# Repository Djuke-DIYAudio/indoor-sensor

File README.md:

# Indoor sensor
This project contains the open source design files of an affordable indoor air sensor that can accurately measure CO2 level, Temperature, Humidity and Pressure. It contains a ESP8266 wi-fi module making it easy to integrate with your home automation system. 

Possible use cases:
* Monitoring sensor values over time
* Switching of air ventilation based on CO2 or humidity level
* Regulating room temperature (airco or heater)

# Design

## Considerations
At the moment the design considerations are:

* MH-Z19 sensor for measuring CO2 ppm
* BME280 sensor for measuring temperature, humidity and pressure sensor
* ESP8266 module to easily integrate with WIFI in the smart home
* red/green dual LED for level indication
  - Green, PPM < 800
  - Yellow/Orange, 800 < PPM < 1400
  - Red, PPM > 1400
* Connectors for optional 0.91 inch or 0.96 inch SSD1306 display
* Sales price around 25 euros

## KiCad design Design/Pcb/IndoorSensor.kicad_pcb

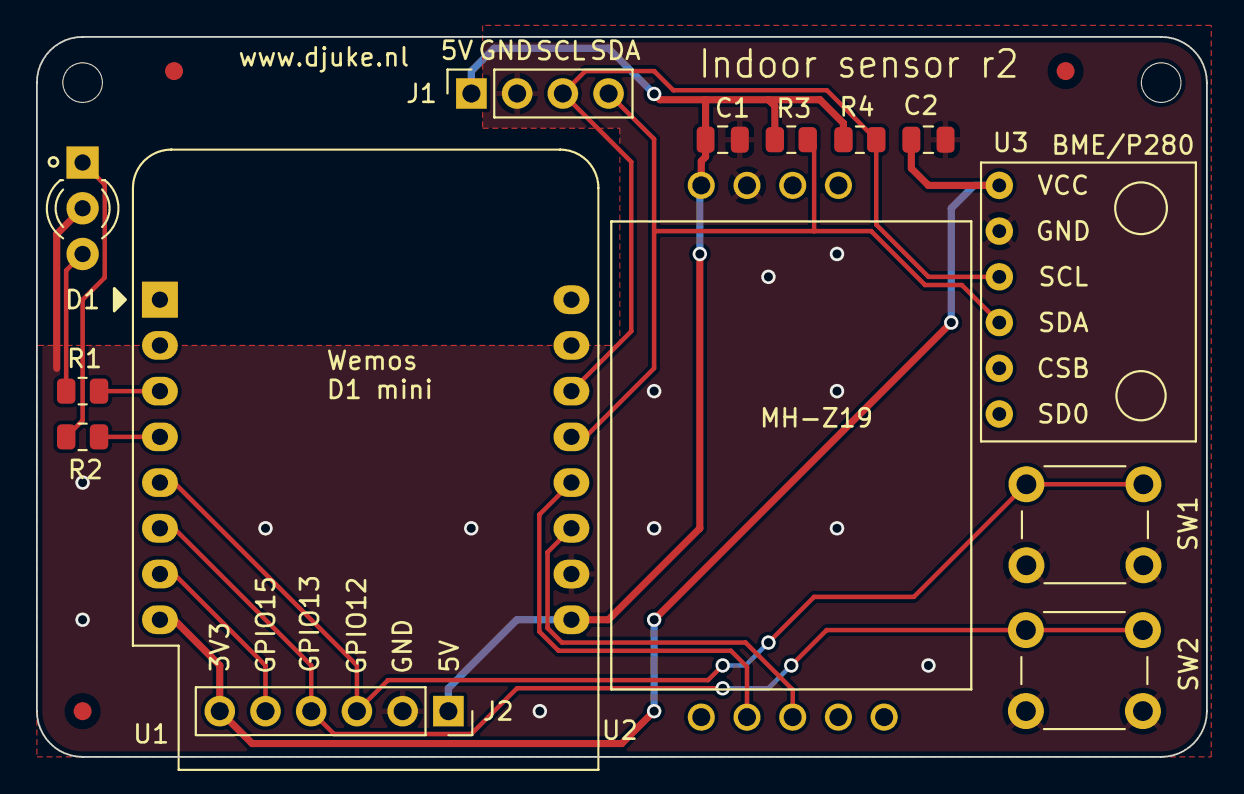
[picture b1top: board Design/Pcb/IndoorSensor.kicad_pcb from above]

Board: 2 copper layers, 65.0 x 40.0 mm, 19 parts (0 on the bottom side), 14 nets.

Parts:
C1, C2: 100n; C_0805_2012Metric
D1: LED_Dual_AKA; LED_D3.0mm-3
FID1, FID2, FID3: Fiducial; Fiducial_1mm_Mask2mm
H1, H2: MountingHole; MountingHole_2.2mm_M2
J1: Conn_01x04_Pin; PinSocket_1x04_P2.54mm_Vertical
J2: Conn_01x06_Pin; PinSocket_1x06_P2.54mm_Vertical
R1, R2: 220; R_0805_2012Metric
R3, R4: 4k7; R_0805_2012Metric
SW1, SW2: SW_Push; SW_PUSH_6mm_H5mm
U1: WeMos_D1_mini; WEMOS_D1_mini_light
U2: MH-Z19B; MH-Z19B-FOOT
U3: module_bme280

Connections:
+3V3: C2.1, J2.6, U1.8 (3V3), U3.1 (VCC)
+5V: C1.1, J1.1, J2.1, R3.2, R4.2, U1.9 (5V), U2.VIN
GND: C1.2, C2.2, D1.2 (K), J1.2, J2.2, SW1.2, SW2.2, U1.10 (GND), U2.GND, U3.2 (GND)
GPIO12: J2.3, SW1.1, U1.5 (MISO/D6)
GPIO13: J2.4, SW2.1, U1.6 (MOSI/D7)
GPIO15: J2.5, U1.7 (CS/D8)
LED_ERR: R2.1, U1.4 (SCK/D5)
LED_OK: R1.1, U1.3 (D0)
unnamed: D1.1 (A1), R2.2
unnamed: D1.3 (A2), R1.2
RX: U1.11 (D4), U2.TX
SCL: J1.3, R4.1, U1.14 (SCL/D1), U3.3 (SCL)
SDA: J1.4, R3.1, U1.13 (SDA/D2), U3.4 (SDA)
TX: U1.12 (D3), U2.RX

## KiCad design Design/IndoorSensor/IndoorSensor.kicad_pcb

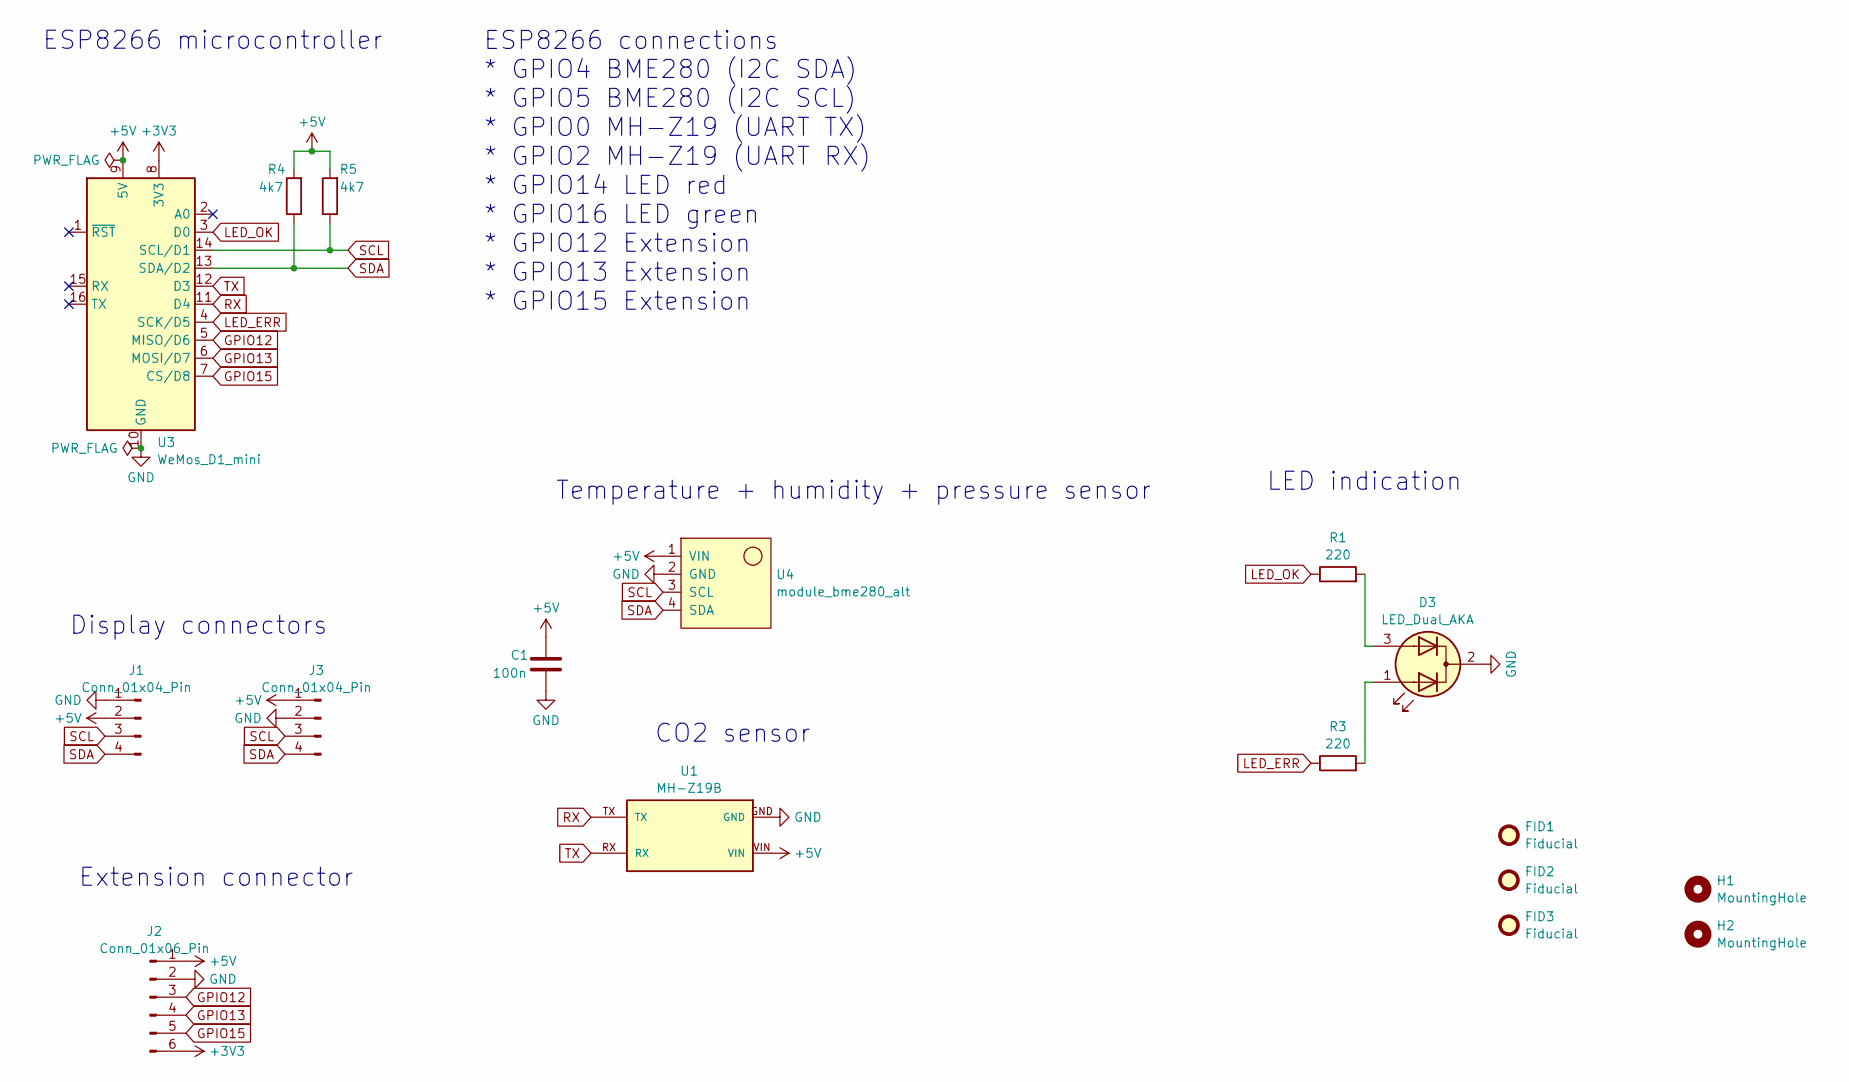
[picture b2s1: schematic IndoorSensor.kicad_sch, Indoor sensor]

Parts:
C1: 100n; C_0805_2012Metric
D3: LED_Dual_AKA; LED_D3.0mm-3
FID1, FID2, FID3: Fiducial; Fiducial_1mm_Mask2mm
H1, H2: MountingHole; MountingHole_2.2mm_M2
J1, J3: Conn_01x04_Pin; PinSocket_1x04_P2.54mm_Vertical
J2: Conn_01x06_Pin; PinHeader_1x06_P2.54mm_Vertical
R1, R3: 220; R_0805_2012Metric
R4, R5: 4k7; R_0805_2012Metric
U1: MH-Z19B; MH-Z19B-FOOT
U3: WeMos_D1_mini; WEMOS_D1_mini_light
U4: module_bme280_alt

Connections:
+3V3: J2.6, U3.8 (3V3)
+5V: C1.1, J1.2, J2.1, J3.1, R4.2, R5.2, U1.VIN, U3.9 (5V), U4.1 (VIN)
GND: C1.2, D3.2 (K), J1.1, J2.2, J3.2, U1.GND, U3.10 (GND), U4.2 (GND)
GPIO12: J2.3, U3.5 (MISO/D6)
GPIO13: J2.4, U3.6 (MOSI/D7)
GPIO15: J2.5, U3.7 (CS/D8)
LED_ERR: R3.1, U3.4 (SCK/D5)
LED_OK: R1.1, U3.3 (D0)
unnamed: D3.1 (A1), R3.2
unnamed: D3.3 (A2), R1.2
RX: U1.TX, U3.11 (D4)
SCL: J1.3, J3.3, R5.1, U3.14 (SCL/D1), U4.3 (SCL)
SDA: J1.4, J3.4, R4.1, U3.13 (SDA/D2), U4.4 (SDA)
TX: U1.RX, U3.12 (D3)

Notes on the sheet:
Temperature + humidity + pressure sensor
ESP8266 connections * GPIO4 BME280 (I2C SDA) * GPIO5 BME280 (I2C SCL) * GPIO0 MH-Z19 (UART TX) * GPIO2 MH-Z19 (UART RX) * GPIO14 LED red * GPIO16 LED green * GPIO12 Extension * GPIO13 Extension * GPIO15 Extension
ESP8266 microcontroller
LED indication
Extension connector
CO2 sensor
Display connectors

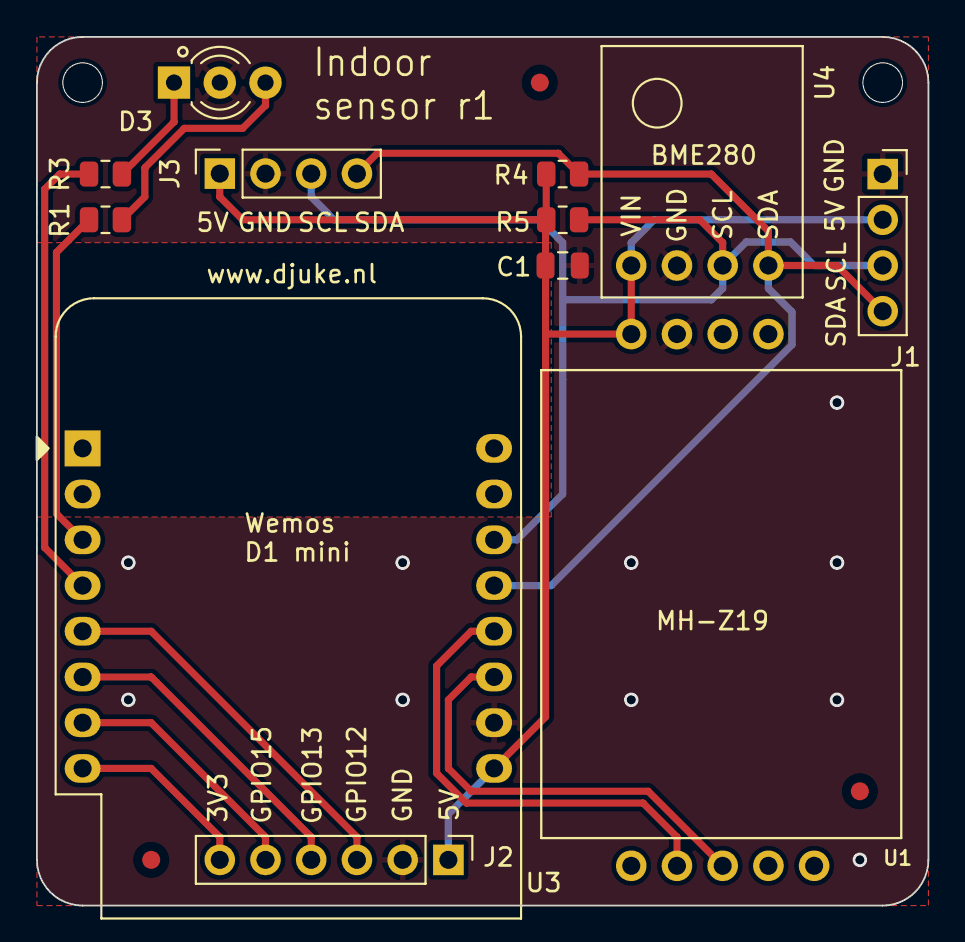
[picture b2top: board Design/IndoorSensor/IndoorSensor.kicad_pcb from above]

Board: 2 copper layers, 49.5 x 48.3 mm, 17 parts (0 on the bottom side), 14 nets.

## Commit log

2024-01-26 Add first indoor sensor design
2024-01-26 Update hole size and 3d references
2024-01-26 Fix minor issues before production
2024-08-08 Move PCB design to different folder
2024-08-08 Add FreeCAD design for the housing
2024-08-08 Add initial ESPhome configuration
2024-08-16 Improve temp offset
2024-12-24 Add revision 2 design
2024-12-24 Final rev2 fixes
2025-02-28 Release Indoor sensor r2
